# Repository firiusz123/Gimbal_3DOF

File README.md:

# Gimbal_3DOF

---

## 📖 Project Description

**Gimbal 3DOF** is a three-axis camera stabilization system (pitch, roll, yaw) designed for integration with drones and small aerial platforms. The goal of the project was to create a modular, lightweight, energy-efficient gimball, for the Project classes of AGH university of science and technology course , Mechatronic Design . The system uses an IMU and servos, controlled by an STM32 microcontroller in the custom PCB , and by Arduino Mega within the prototype , both running with FreeRTOS. A Python-based graphical user interface (GUI) is also provided for testing and interaction. The working model present on the provided photos is a prototype that doesnt have the custom PCB that has been designed

---

## ⚙️ Features

- 3-axis stabilization: **Pitch**, **Roll**, and **Yaw**
- Supports cameras up to **200 g**
- Compact size: **30 × 10 × 15 cm**
- Lightweight design: **~200 g**
- Power consumption: **~900 mA** estimated for worst case scenario
- UART-based communication
- Rubber-based vibration damping system
- Python GUI for testing and position control
- FreeRTOS-based multithreaded control system
- Optimized weight distribution and center of mass

---

## 🧾 Requirements

### Hardware with custom PCB

| Component           | Model / Notes                    |
|---------------------|----------------------------------|
| Microcontroller     | STM32G431CBT6                    |
| IMU Sensor          | IMU 9DOF v2.0                    |
| Servos              | Feetech FS510R ×3                |
| Oscillator          | 8 MHz WE-XTAL                    |
| PCB                 | Custom PCB or Arduino prototype  |
| Logic level shifters| 2× SN74LV1T34                    |
| Vibration dampers   | Silicone-based, hand-cut         |

### Hardware of Prototype

| Component           | Model / Notes                    |
|---------------------|----------------------------------|
| Board               | Arduino Mega                     |
| IMU Sensor          | IMU 9DOF v2.0                    |
| Servos              | Feetech FS510R ×3                |
| LM7805              | 5v Linear Stabilizator           |
| 7.4 v lipo          | a small lipo battery 2s          |

### Connection scheme for the prototype 
#### 🧭 Servo Motor Pinout

| Servo Axis | Signal Pin (Arduino) | VCC (5 V from LM7805) | GND (Common Ground) |
|------------|----------------------|------------------------|----------------------|
| Roll       | D9                   | LM7805 OUT             | LM7805 GND           |
| Pitch      | D10                  | LM7805 OUT             | LM7805 GND           |
| Yaw        | D2                   | LM7805 OUT             | LM7805 GND           |

---

### ⚡ Power Supply Setup (LM7805)

| LM7805 Pin | Connects To                                      |
|------------|--------------------------------------------------|
| **IN**     | 7.4 V battery (+)                                |
| **OUT**    | - 5 V to all Servo VCC pins  <br> - 5 V to Arduino **VIN** *(optional)* |
| **GND**    | - Battery (–) <br> - All Servo GND pins <br> - Arduino **GND** |

The connection from 5v to vin is optional since the power to arduino is also delivered via cable that sends the commands to arduino 

### Software

- FreeRTOS (embedded)
- Python GUI for control and testing
- Source code (C / Arduino)

---

## 💻 Usage

1. Connect all components using the provided PCB or wire manually according to the schematic.
2. Upload the firmware from the `Arduino_example\GimbalControl1` directory to the Arduino.
3. Launch the GUI from the `python_gui` directory for testing and IMU visualization.
4. The gimbal continuously reads IMU data and stabilizes the camera accordingly.
5. You can also send specific positions for the gimbal to hold using the GUI.

---

## 🧩 Hardware & Software

**Hardware:**
- FS510R servos provide accurate positioning with low power consumption.
- IMU 9DOF v2.0 offers compact size, low power, and acceptable precision.
- Custom PCB integrates all components for clean wiring and scalability.
- Silicone dampers mitigate mechanical vibrations from drone operation.

**Software:**
- Based on FreeRTOS – enables independent control of each axis.
- Python GUI allows sending positions, reading IMU data, and system testing.
- All code is available in the `Arduino_example` and `python_gui` directories.

---

## 📈  Simulations

The project included modal simulations (FEM) using Siemens NX. These simulations helped with:

- Identifying modal frequencies (especially around **700 Hz**) and ensuring the control loop (**100 Hz**) avoids them.
- Optimizing the gimbal’s mass distribution and weight balancing.
- Evaluating dynamic response under two critical configurations (extreme pitch/yaw).

Simulation results guided mechanical redesigns and ensured robustness in real-world operation.

---

## 🖼️ Prototype Images

### ✅ Final prototype mounted on a drone:

### 🛠️ Printed components:

### 🖥️ GUI for testing and visualization:

## FEM Analisys
FEM analysis of the mechatronic system was performed. Specifically, the mode vibration analysis using Siemens NX software. The system was analyzed in two configurations. Bellow we list a few illustrations showing NX environment:

.png)
---

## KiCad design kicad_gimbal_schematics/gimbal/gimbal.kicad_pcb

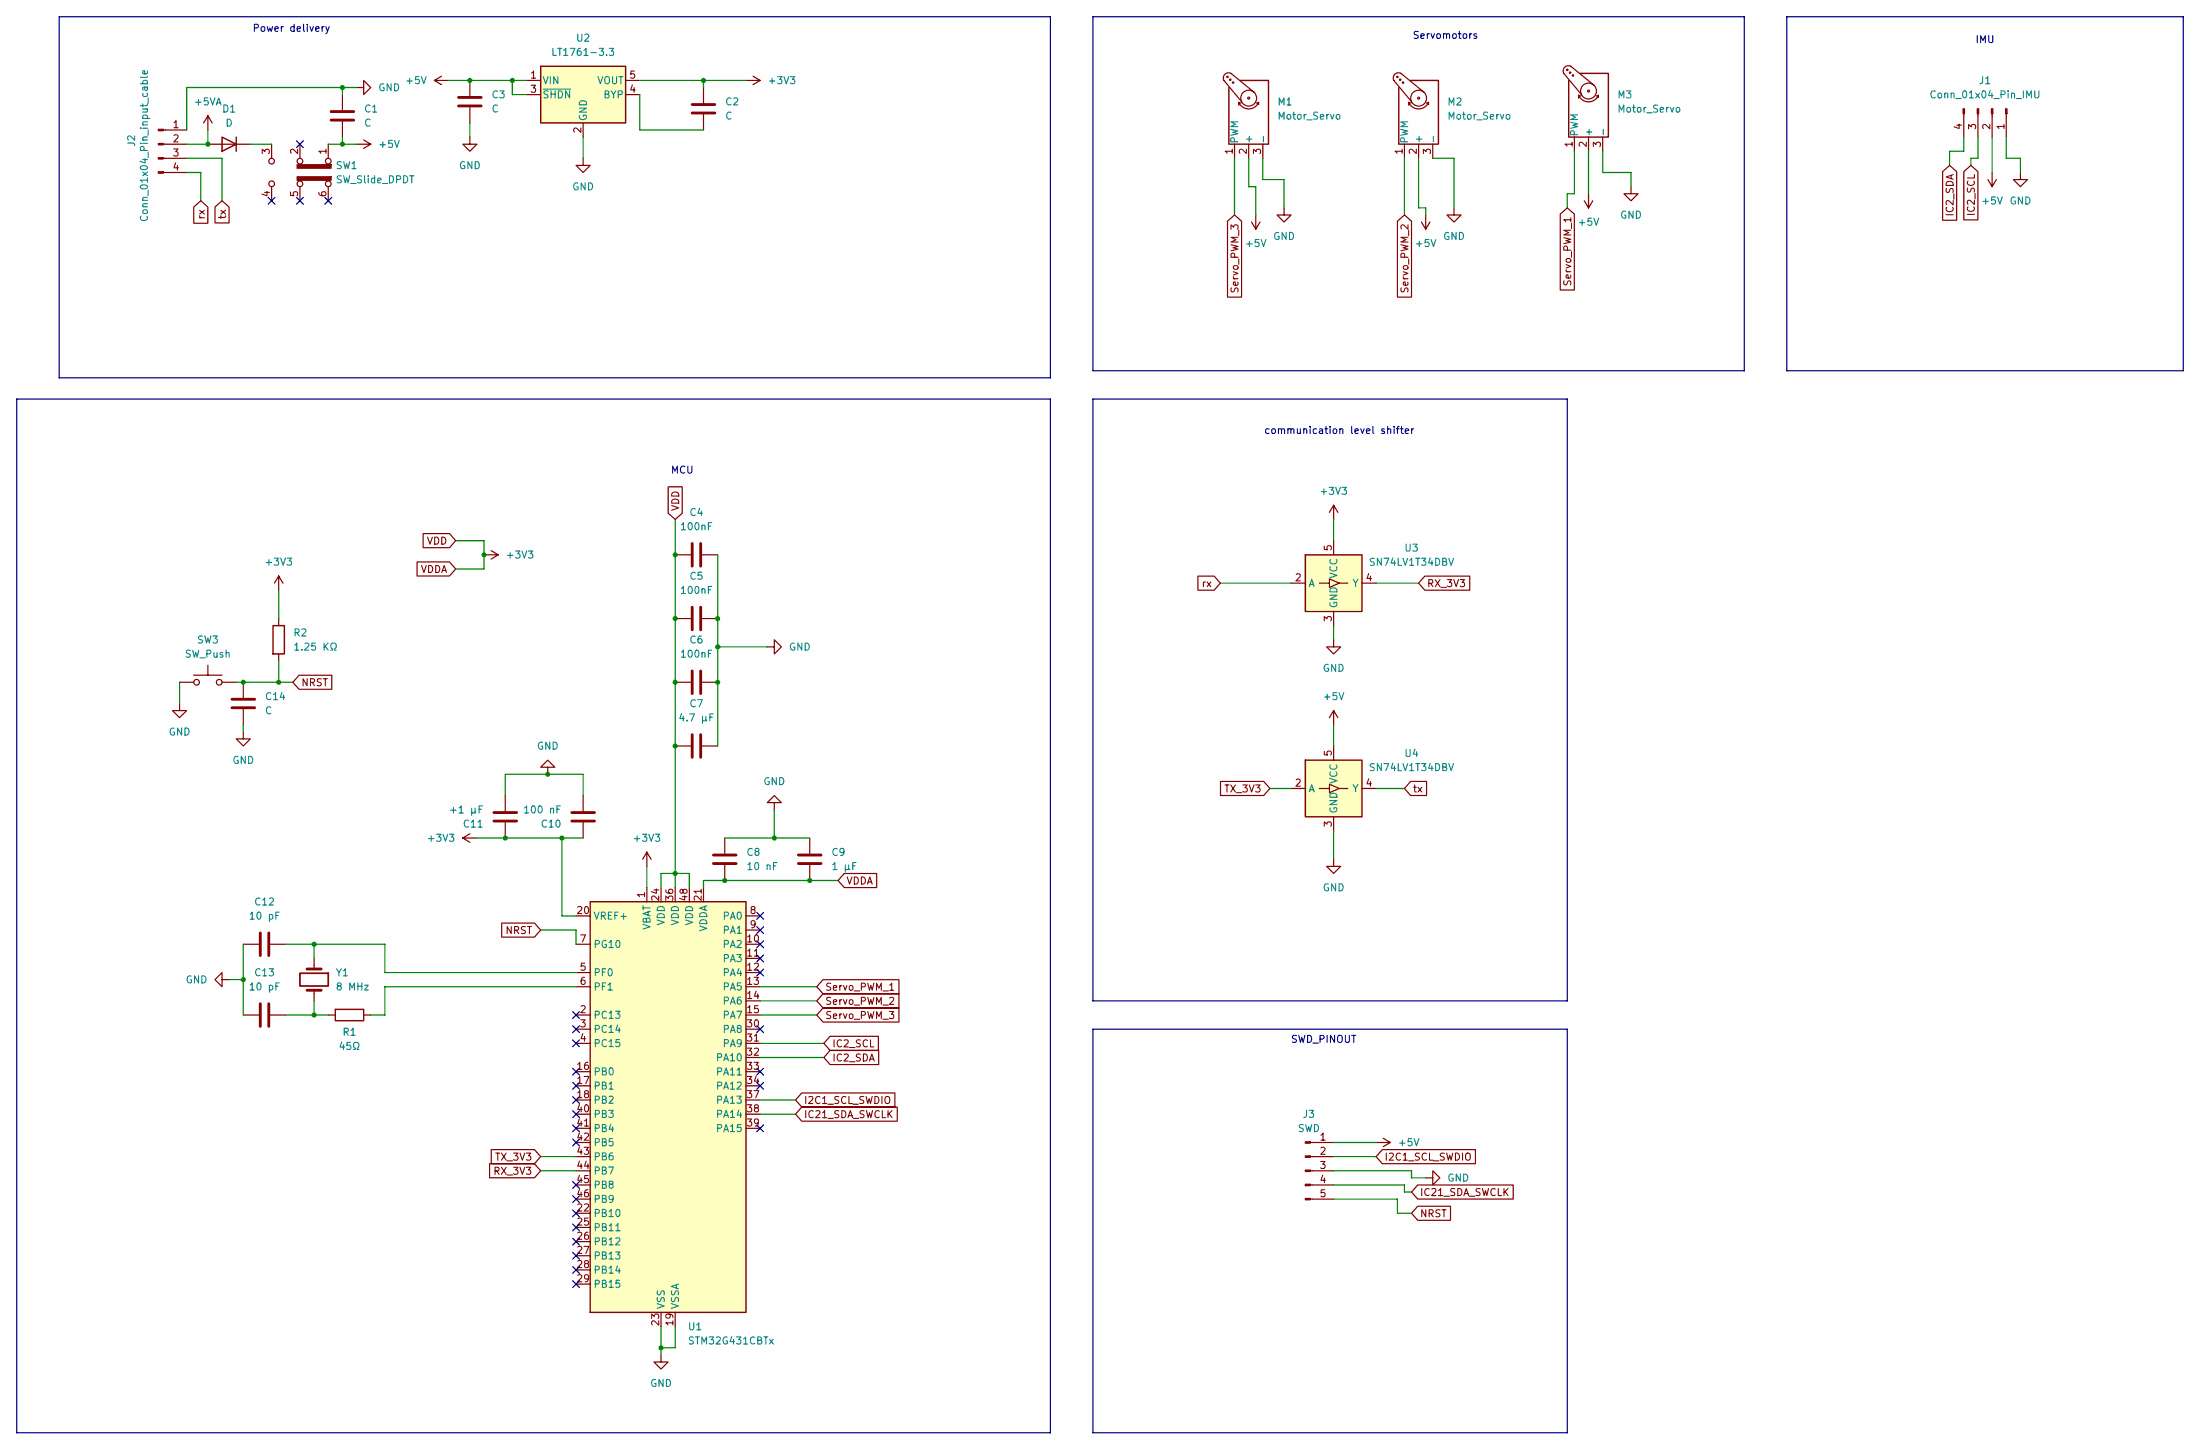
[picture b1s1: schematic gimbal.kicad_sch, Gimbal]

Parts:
C1, C2, C3: C; C_0805_2012Metric
C4, C5, C6: 100nF; C_0805_2012Metric
C7: 4.7 μF; C_0805_2012Metric
C8: 10 nF; C_0805_2012Metric
C9: 1 μF; C_0805_2012Metric
C10: 100 nF; C_0805_2012Metric
C11: +1 μF; C_0805_2012Metric
C12, C13: 10 pF; C_0805_2012Metric
C14: C; C_0805_2012Metric_Pad1.18x1.45mm_HandSolder
D1: D; D_0805_2012Metric
J1: Conn_01x04_Pin_IMU; PinHeader_1x04_P2.54mm_Vertical
J2: Conn_01x04_Pin_input_cable; PinHeader_1x04_P2.54mm_Vertical
J3: SWD; PinHeader_1x05_P2.54mm_Vertical
M1, M2, M3: Motor_Servo; PinHeader_1x03_P2.54mm_Vertical
R1: 45Ω; R_0805_2012Metric
R2: 1.25 KΩ; R_0805_2012Metric_Pad1.20x1.40mm_HandSolder
SW1: SW_Slide_DPDT; SW_CK_JS202011CQN_DPDT_Straight
SW3: SW_Push; SW_SPST_B3U-1000P
U1: STM32G431CBTx; LQFP-48_7x7mm_P0.5mm
U2: LT1761-3.3; TSOT-23-5
U3, U4: SN74LV1T34DBV; SOT-23-5
Y1: 8 MHz; Crystal_SMD_0603-2Pin_6.0x3.5mm

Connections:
+5V: C1.1, C3.1, J1.2, J3.1, M1.2 (+), M2.2 (+), M3.2 (+), SW1.1 (A), U2.1 (VIN), U2.3 (~SHDN), U4.5 (VCC)
+5VA: D1.2 (A), J2.2
GND: C1.2, C3.2, C4.1, C5.1, C6.1, C7.1, C8.1, C9.1, C10.1, C11.1, C12.2, C13.2, C14.2, J1.1, J2.1, J3.3, M1.3 (-), M2.3 (-), M3.3 (-), SW3.1, U1.19 (VSSA), U1.23 (VSS), U1.35 (VSS), U1.47 (VSS), U2.2 (GND), U3.3 (GND), U4.3 (GND)
I2C1_SCL_SWDIO: J3.2, U1.37 (PA13)
IC2_SCL: J1.3, U1.31 (PA9)
IC2_SDA: J1.4, U1.32 (PA10)
IC21_SDA_SWCLK: J3.4, U1.38 (PA14)
NRST: C14.1, J3.5, R2.2, SW3.2, U1.7 (PG10)
unnamed: C13.1, R1.2, Y1.2
unnamed: D1.1 (K), SW1.3 (C)
unnamed: C12.1, U1.5 (PF0), Y1.1
unnamed: R1.1, U1.6 (PF1)
unnamed: C2.2, U2.4 (BYP)
RX_3V3: U1.44 (PB7), U3.4 (Y)
Servo_PWM_1: M3.1 (PWM), U1.13 (PA5)
Servo_PWM_2: M2.1 (PWM), U1.14 (PA6)
Servo_PWM_3: M1.1 (PWM), U1.15 (PA7)
TX_3V3: U1.43 (PB6), U4.2 (A)
VDD: C2.1, C4.2, C5.2, C6.2, C7.2, C8.2, C9.2, C10.2, C11.2, R2.1, U1.1 (VBAT), U1.20 (VREF+), U1.21 (VDDA), U1.24 (VDD), U1.36 (VDD), U1.48 (VDD), U2.5 (VOUT), U3.5 (VCC)
rx: J2.4, U3.2 (A)
tx: J2.3, U4.4 (Y)

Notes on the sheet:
communication level shifter
SWD_PINOUT
Servomotors
IMU
MCU
Power delivery

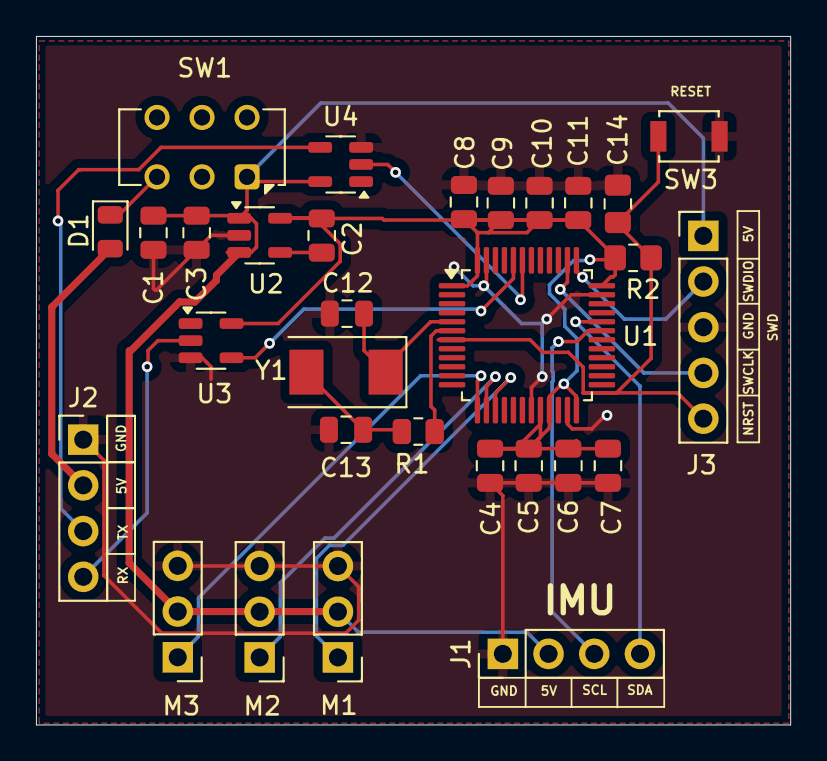
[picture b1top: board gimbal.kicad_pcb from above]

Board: 2 copper layers, 41.9 x 38.2 mm, 30 parts (0 on the bottom side), 21 nets.

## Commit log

2025-05-26 added gitignore
2025-05-26 added gitignore again
2025-05-26 normal commit
2025-05-26 gitignore update
2025-05-26 removing uneccesary dir
2025-05-26 removing unecessary files
2025-05-26 removing unecessary files again
2025-06-03 changed arduino parser
2025-06-05 Added a patch to plotting and threading, plot starts from 0 now and threads shut down gracefully
2025-06-12 name clean-up
2025-06-12 Adding CAD stuff
2025-07-08 added images for readme
2025-07-08 adding extra image for readme
2025-07-20 More and higher quality media files
